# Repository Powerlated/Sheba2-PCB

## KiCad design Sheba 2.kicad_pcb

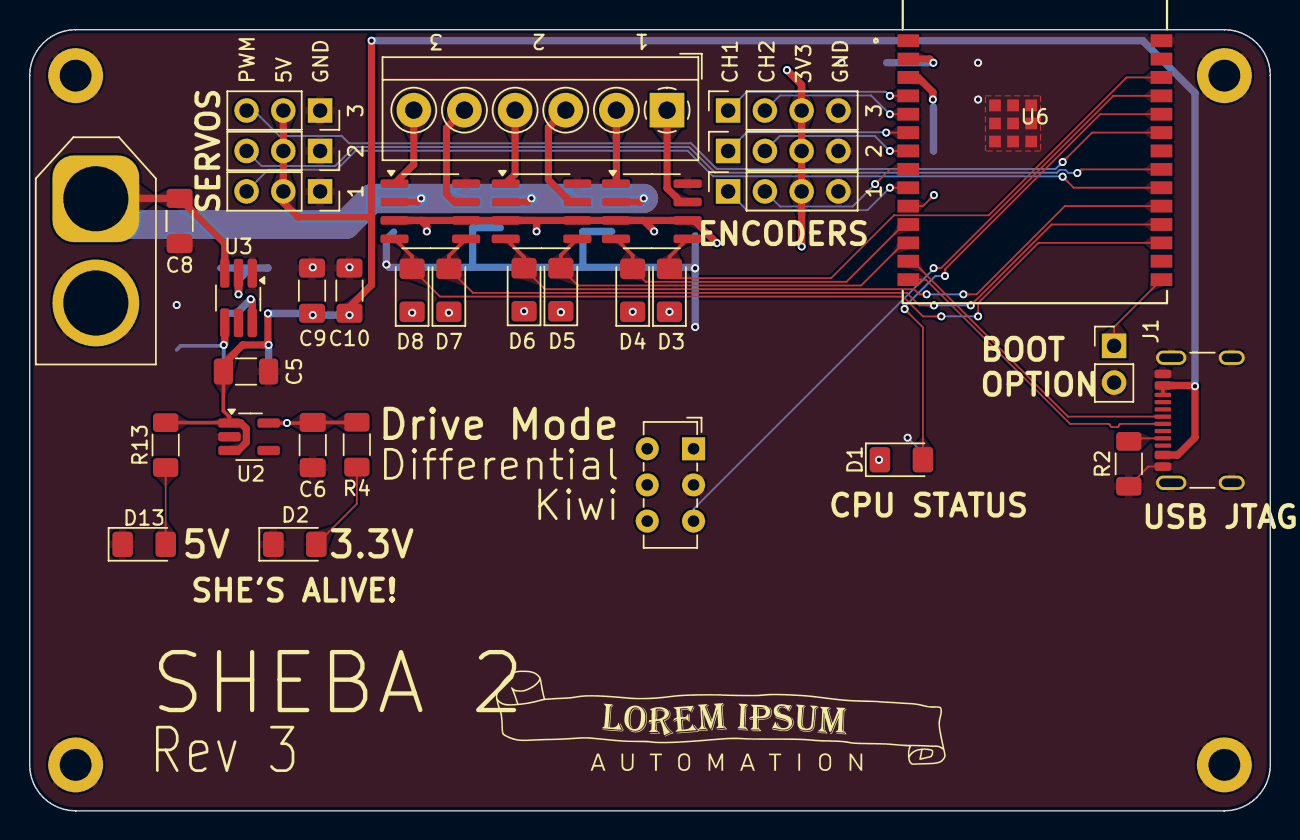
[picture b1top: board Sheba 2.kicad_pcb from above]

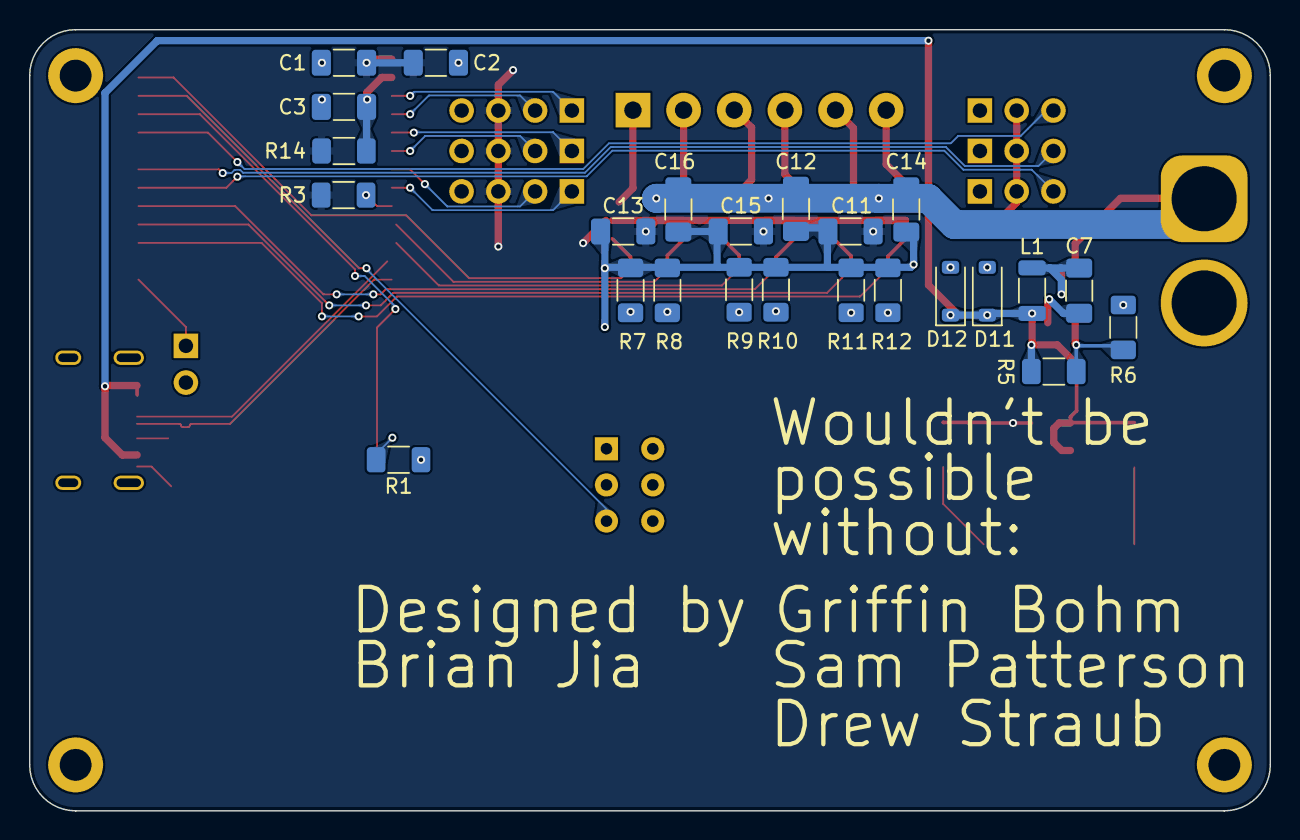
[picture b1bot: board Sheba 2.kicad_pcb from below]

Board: 2 copper layers, 85.7 x 54.0 mm, 62 parts (24 on the bottom side), 45 nets.

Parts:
Battery1: XT-60; AMASS_XT60-F_1x02_P7.20mm_Vertical
C1, C8, C9, C10: C22uF; C_1206_3216Metric_Pad1.33x1.80mm_HandSolder
C2, C3, C5, C6, C7, C11, C12, C13, C14, C15, C16: C1uF; C_1206_3216Metric_Pad1.33x1.80mm_HandSolder
D1, D2, D3, D5, D7, D13: LED Green; LED_1206_3216Metric_Pad1.42x1.75mm_HandSolder
D4, D6, D8: LED Red; LED_1206_3216Metric_Pad1.42x1.75mm_HandSolder
D11, D12: D_Zener5V; D_SOD-123
EP1, EP2, EP3: Conn_01x04_Socket; PinSocket_1x04_P2.54mm_Vertical
H1, H2, H3, H4: MountingHole_Pad; MountingHole_2.2mm_M2_DIN965_Pad
J1: Conn_01x02_Pin; PinHeader_1x02_P2.54mm_Vertical
J4, J5, J6: Conn_01x03_Pin; PinSocket_1x03_P2.54mm_Vertical
L1: L3.3uH; L_1206_3216Metric
MD1, MD2, MD3: ZXBM5210-S; SOIC-8_3.9x4.9mm_P1.27mm
Motor Terminal1: 6x Motor Port; TerminalBlock_4Ucon_1x06_P3.50mm_Horizontal
P1: USB 2.0 Type-C Port; USB_C_Receptacle_GCT_USB4105-xx-A_16P_TopMnt_Horizontal
R1, R4, R7, R8, R9, R10, R11, R12, R13: R220; R_1206_3216Metric_Pad1.30x1.75mm_HandSolder
R2: R5.11K; R_1206_3216Metric_Pad1.30x1.75mm_HandSolder
R3, R6, R14: R10k; R_1206_3216Metric_Pad1.30x1.75mm_HandSolder
R5: R56.2k; R_1206_3216Metric_Pad1.30x1.75mm_HandSolder
SW1: SPDT Switch; SW_E-Switch_EG1271_SPDT
U2: MIC5504-3.3YM5; SOT-23-5_HandSoldering
U3: AP62300TWU; TSOT-23-6_HandSoldering
U6: ESP32-C6-WROOM-1-N4; MOD28_ESP32-C6-WROOM-1_EXP

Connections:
+3V3: C1.2, C2.2, C6.1, C11.1, C13.1, C15.1, EP1.3, EP2.3, EP3.3, MD1.3 (VDD), MD1.6 (VREF), MD2.3 (VDD), MD2.6 (VREF), MD3.3 (VDD), MD3.6 (VREF), R3.1, R4.1, R14.1, U2.5 (VOUT), U6.2 (3V3)
+5V: C5.1, C9.1, C10.1, D11.1 (K), D12.1 (K), J4.2, J5.2, J6.2, L1.2, P1.A4 (VBUS), P1.A9 (VBUS), P1.B4 (VBUS), P1.B5 (VCONN), P1.B9 (VBUS), R5.1, R13.1, U2.1 (VIN), U2.3 (EN)
+BATT: Battery1.1 (+), C8.1, C12.1, C14.1, C16.1, MD1.2 (VM), MD2.2 (VM), MD3.2 (VM), U3.3 (IN)
/Power & Motors/M1_OUT1: MD3.7 (OUT2), Motor Terminal1.1
/Power & Motors/M1_OUT2: MD3.1 (OUT1), Motor Terminal1.2
/Power & Motors/M2_OUT1: MD2.7 (OUT2), Motor Terminal1.3
/Power & Motors/M2_OUT2: MD2.1 (OUT1), Motor Terminal1.4
/Power & Motors/M3_OUT1: MD1.7 (OUT2), Motor Terminal1.5
/Power & Motors/M3_OUT2: MD1.1 (OUT1), Motor Terminal1.6
BLINKY: D1.2 (A), U6.24 (RXD0)
BOOT_OPTION: J1.1, U6.15 (IO9)
EN: C3.2, R14.2, U6.3 (EN)
ENC1_1: EP1.1, U6.9 (IO1)
ENC1_2: EP1.2, U6.8 (IO0)
ENC2_1: EP2.1, U6.6 (IO6)
ENC2_2: EP2.2, U6.7 (IO7)
ENC3_1: EP3.1, U6.4 (IO4)
ENC3_2: EP3.2, U6.5 (IO5)
GND: Battery1.2 (-), C1.1, C2.1, C3.1, C5.2, C6.2, C8.2, C9.2, C10.2, C11.2, C12.2, C13.2, C14.2, C15.2, C16.2, D2.1 (K), D11.2 (A), D12.2 (A), D13.1 (K), EP1.4, EP2.4, EP3.4, H1.1, H2.1, H3.1, H4.1, J1.2, J4.1, J5.1, J6.1, MD1.8 (GND), MD2.8 (GND), MD3.8 (GND), P1.A1 (GND), P1.A12 (GND), P1.B1 (GND), P1.B12 (GND), P1.S1 (SHIELD), R1.2, R2.1, R6.2, R7.2, R8.2, R9.2, R10.2, R11.2, R12.2, SW1.2 (B), U2.2 (GND), U3.1 (GND), U6.1 (GND), U6.28 (GND), U6.29 (GND), U6.30 (GND), U6.31 (GND), U6.32 (GND), U6.33 (GND), U6.34 (GND), U6.35 (GND), U6.36 (GND), U6.37 (GND)
KIWI_DRIVE: SW1.3 (C), U6.25 (TXD0)
M1_FWD: D3.2 (A), MD3.5 (REV), U6.26 (IO3)
M1_REV: D4.2 (A), MD3.4 (FWD), U6.11 (IO10)
M2_FWD: D5.2 (A), MD2.5 (REV), U6.12 (IO11)
M2_REV: D6.2 (A), MD2.4 (FWD), U6.19 (IO21)
M3_FWD: D7.2 (A), MD1.5 (REV), U6.18 (IO20)
M3_REV: D8.2 (A), MD1.4 (FWD), U6.17 (IO19)
unnamed: D1.1 (K), R1.1
unnamed: D2.2 (A), R4.2
unnamed: D3.1 (K), R7.1
unnamed: D4.1 (K), R8.1
unnamed: D5.1 (K), R9.1
unnamed: D6.1 (K), R10.1
unnamed: D7.1 (K), R11.1
unnamed: D8.1 (K), R12.1
unnamed: D13.2 (A), R13.2
unnamed: P1.A5 (CC), R2.2
unnamed: C7.2, U3.6 (BST)
unnamed: R5.2, R6.1, U3.4 (FB)
unnamed: C7.1, L1.1, U3.2 (SW)
unnamed: R3.2, U6.10 (IO8)
SERVO1: J6.3, U6.23 (IO15)
SERVO2: J4.3, U6.21 (IO23)
SERVO3: J5.3, U6.20 (IO22)
USB_D+: P1.A6 (D+), U6.14 (IO13)
USB_D-: P1.A7 (D-), U6.13 (IO12)

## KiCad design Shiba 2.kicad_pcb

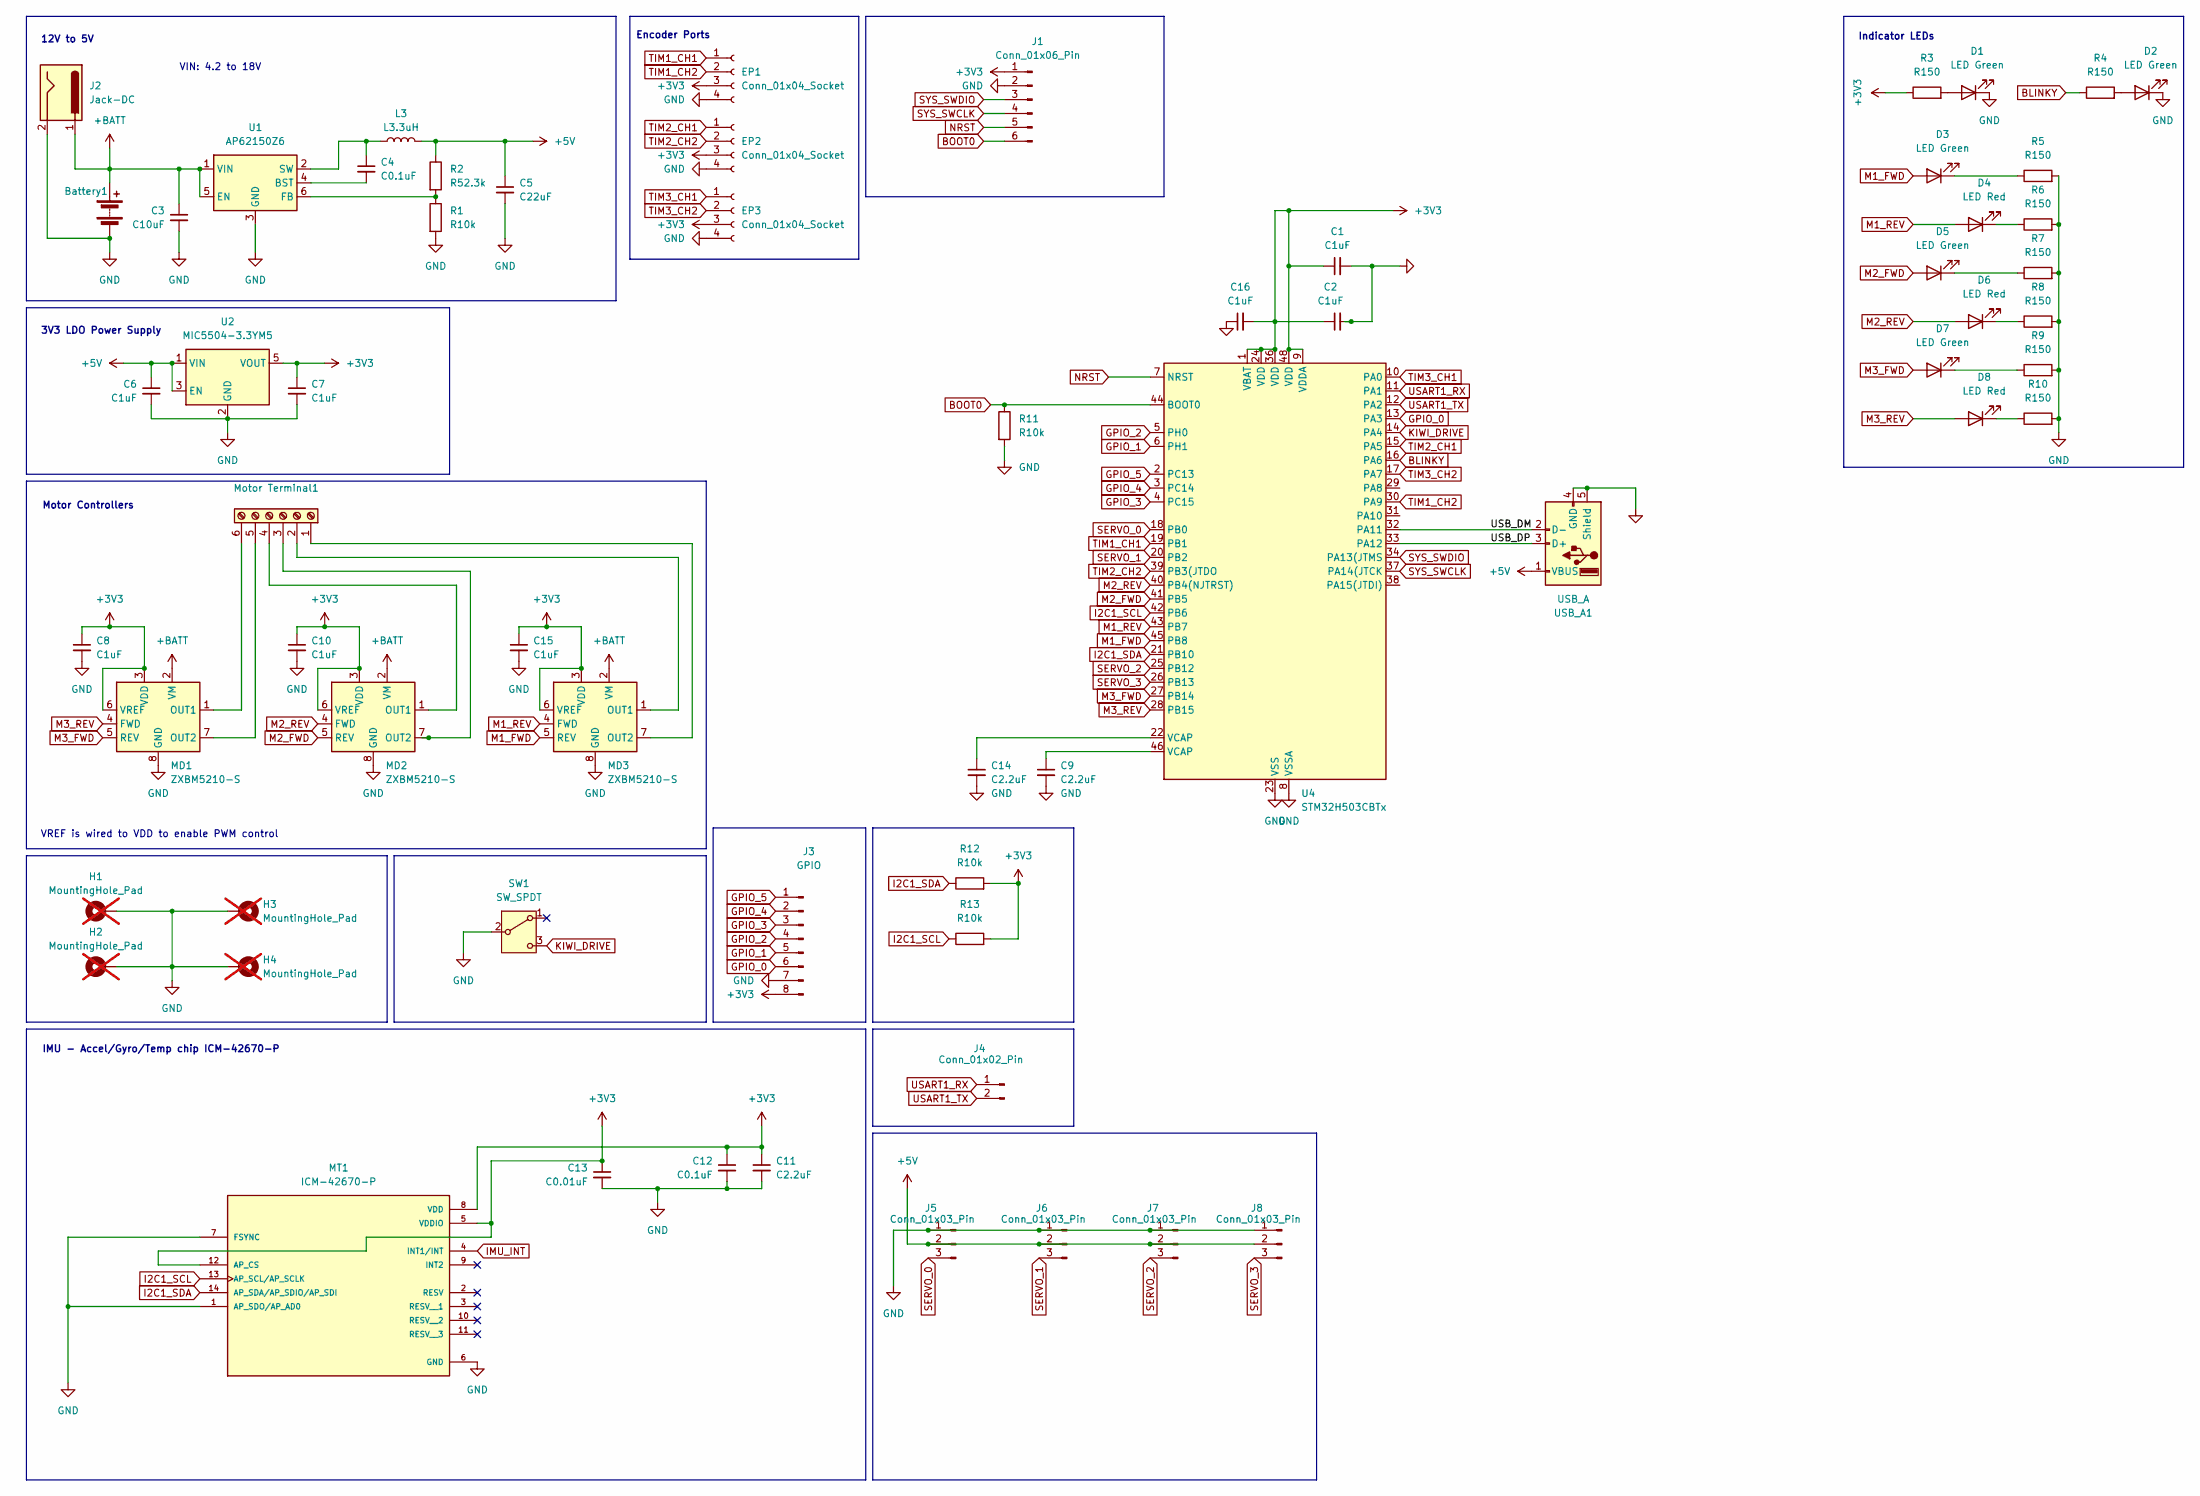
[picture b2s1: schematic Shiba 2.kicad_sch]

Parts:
Battery1: AMASS_XT60-F_1x02_P7.20mm_Vertical; DigiKey PRT-10474
C1, C2, C6, C7, C8, C10, C15, C16: C1uF; C_1206_3216Metric_Pad1.33x1.80mm_HandSolder; DigiKey CL31B105KBHNNNE
C3: C10uF; C_1206_3216Metric_Pad1.33x1.80mm_HandSolder; DigiKey CL31B106KOHNNWE
C4, C12: C0.1uF; C_1206_3216Metric_Pad1.33x1.80mm_HandSolder; DigiKey C1206C104K5RAC7800
C5: C22uF; C_1206_3216Metric_Pad1.33x1.80mm_HandSolder; DigiKey CL31A226MOCLNNC
C9, C14: C2.2uF; C_1206_3216Metric_Pad1.33x1.80mm_HandSolder; DigiKey CL31B105KBHNNNE
C11: C2.2uF; C_1206_3216Metric_Pad1.33x1.80mm_HandSolder; DigiKey CL31B225KBHNFNE
C13: C0.01uF; C_1206_3216Metric_Pad1.33x1.80mm_HandSolder; DigiKey C1206C103K5RAC7025
D1, D2, D3, D5, D7: LED Green; LED_1206_3216Metric_Pad1.42x1.75mm_HandSolder; DigiKey 150120VS75000
D4, D6, D8: LED Red; LED_1206_3216Metric_Pad1.42x1.75mm_HandSolder; DigiKey 150120RS75000
EP1, EP2, EP3: Conn_01x04_Socket; PinSocket_1x04_P2.54mm_Vertical; DigiKey 2.54mm Pin Socket
H1, H2, H3, H4: MountingHole_Pad; MountingHole_2.2mm_M2_DIN965_Pad; not fitted
J1: Conn_01x06_Pin; PinHeader_1x06_P2.54mm_Vertical; DigiKey 2.54mm Pin Header
J2: Jack-DC; BarrelJack_CUI_PJ-063AH_Horizontal; DigiKey PJ-037A
J3: GPIO; PinSocket_1x08_P2.54mm_Vertical; DigiKey 2.54mm Pin Socket
J4: Conn_01x02_Pin; PinHeader_1x02_P2.54mm_Vertical; DigiKey 2.54mm Pin Socket
J5, J6, J7, J8: Conn_01x03_Pin; PinSocket_1x03_P2.54mm_Vertical; DigiKey 2.54mm Pin Socket
L3: L3.3uH; L_1206_3216Metric; DigiKey LQM31PN3R3M00L
MD1, MD2, MD3: ZXBM5210-S; SOIC-8_3.9x4.9mm_P1.27mm; DigiKey ZXBM5210-S-1
MT1: ICM-42670-P; XDCR_ICM-42670-P; PARTREV 1.1; DigiKey ICM-42670-P
Motor Terminal1: TerminalBlock_4Ucon_1x06_P3.50mm_Horizontal; DigiKey OQ0612510000G
R1, R11, R12, R13: R10k; R_1206_3216Metric_Pad1.30x1.75mm_HandSolder; DigiKey RC1206FR-0710KL
R2: R52.3k; R_1206_3216Metric_Pad1.30x1.75mm_HandSolder; DigiKey CRCW120652K3FKEA
R3, R4, R5, R6, R7, R8, R9, R10: R150; R_1206_3216Metric_Pad1.30x1.75mm_HandSolder; DigiKey P150BCCT-ND
SW1: SW_SPDT; SW_E-Switch_EG1271_SPDT; DigiKey EG1271A
U1: AP62150Z6; SOT-563; DigiKey AP62150Z6-7
U2: MIC5504-3.3YM5; SOT-23-5; DigiKey MIC5504-3.3YM5
U4: STM32H503CBTx; LQFP-48_7x7mm_P0.5mm
USB_A1: USB_A; USB_A_Receptacle_GCT_USB1046; DigiKey USB-A1HSB6

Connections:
+3V3: C1.1, C2.1, C7.1, C8.1, C10.1, C11.1, C12.1, C13.1, C15.1, C16.2, EP1.3, EP2.3, EP3.3, J1.1, J3.8, MD1.3 (VDD), MD1.6 (VREF), MD2.3 (VDD), MD2.6 (VREF), MD3.3 (VDD), MD3.6 (VREF), MT1.5 (VDDIO), MT1.8 (VDD), MT1.12 (AP_CS), R3.1, R12.2, R13.2, U2.5 (VOUT), U4.1 (VBAT), U4.9 (VDDA), U4.24 (VDD), U4.36 (VDD), U4.48 (VDD)
+5V: C5.1, C6.1, J5.2, J6.2, J7.2, J8.2, L3.2, R2.1, U2.1 (VIN), U2.3 (EN), USB_A1.1 (VBUS)
+BATT: Battery1.1 (+), C3.1, J2.1, MD1.2 (VM), MD2.2 (VM), MD3.2 (VM), U1.1 (VIN), U1.5 (EN)
/USB_DM: U4.32 (PA11), USB_A1.2 (D-)
/USB_DP: U4.33 (PA12), USB_A1.3 (D+)
BLINKY: R4.1, U4.16 (PA6)
BOOT0: J1.6, R11.1, U4.44 (BOOT0)
GND: Battery1.2 (-), C1.2, C2.2, C3.2, C5.2, C6.2, C7.2, C8.2, C9.2, C10.2, C11.2, C12.2, C13.2, C14.2, C15.2, C16.1, D1.1 (K), D2.1 (K), EP1.4, EP2.4, EP3.4, H1.1, H2.1, H3.1, H4.1, J1.2, J2.2, J3.7, J5.1, J6.1, J7.1, J8.1, MD1.8 (GND), MD2.8 (GND), MD3.8 (GND), MT1.1 (AP_SDO/AP_AD0), MT1.6 (GND), MT1.7 (FSYNC), R1.2, R5.2, R6.2, R7.2, R8.2, R9.2, R10.2, R11.2, SW1.2 (B), U1.3 (GND), U2.2 (GND), U4.8 (VSSA), U4.23 (VSS), U4.35 (VSS), U4.47 (VSS), USB_A1.4 (GND), USB_A1.5 (Shield)
GPIO_0: J3.6, U4.13 (PA3)
GPIO_1: J3.5, U4.6 (PH1)
GPIO_2: J3.4, U4.5 (PH0)
GPIO_3: J3.3, U4.4 (PC15)
GPIO_4: J3.2, U4.3 (PC14)
GPIO_5: J3.1, U4.2 (PC13)
I2C1_SCL: MT1.13 (AP_SCL/AP_SCLK), R13.1, U4.42 (PB6)
I2C1_SDA: MT1.14 (AP_SDA/AP_SDIO/AP_SDI), R12.1, U4.21 (PB10)
IMU_INT: MT1.4 (INT1/INT)
KIWI_DRIVE: SW1.3 (C), U4.14 (PA4)
M1_FWD: D3.2 (A), MD3.5 (REV), U4.45 (PB8)
M1_REV: D4.2 (A), MD3.4 (FWD), U4.43 (PB7)
M2_FWD: D5.2 (A), MD2.5 (REV), U4.41 (PB5)
M2_REV: D6.2 (A), MD2.4 (FWD), U4.40 (PB4(NJTRST))
M3_FWD: D7.2 (A), MD1.5 (REV), U4.27 (PB14)
M3_REV: D8.2 (A), MD1.4 (FWD), U4.28 (PB15)
NRST: J1.5, U4.7 (NRST)
unnamed: C9.1, U4.46 (VCAP)
unnamed: C14.1, U4.22 (VCAP)
unnamed: D1.2 (A), R3.2
unnamed: D2.2 (A), R4.2
unnamed: D3.1 (K), R5.1
unnamed: D4.1 (K), R6.1
unnamed: D5.1 (K), R7.1
unnamed: D6.1 (K), R8.1
unnamed: D7.1 (K), R9.1
unnamed: D8.1 (K), R10.1
unnamed: MD1.1 (OUT1), Motor Terminal1.6
unnamed: MD1.7 (OUT2), Motor Terminal1.5
unnamed: MD2.1 (OUT1), Motor Terminal1.4
unnamed: MD2.7 (OUT2), Motor Terminal1.3
unnamed: MD3.1 (OUT1), Motor Terminal1.2
unnamed: MD3.7 (OUT2), Motor Terminal1.1
unnamed: C4.2, U1.4 (BST)
unnamed: R1.1, R2.2, U1.6 (FB)
unnamed: C4.1, L3.1, U1.2 (SW)
SERVO_0: J5.3, U4.18 (PB0)
SERVO_1: J6.3, U4.20 (PB2)
SERVO_2: J7.3, U4.25 (PB12)
SERVO_3: J8.3, U4.26 (PB13)
SYS_SWCLK: J1.4, U4.37 (PA14(JTCK)
SYS_SWDIO: J1.3, U4.34 (PA13(JTMS)
TIM1_CH1: EP1.1, U4.19 (PB1)
TIM1_CH2: EP1.2, U4.30 (PA9)
TIM2_CH1: EP2.1, U4.15 (PA5)
TIM2_CH2: EP2.2, U4.39 (PB3(JTDO)
TIM3_CH1: EP3.1, U4.10 (PA0)
TIM3_CH2: EP3.2, U4.17 (PA7)
USART1_RX: J4.1, U4.11 (PA1)
USART1_TX: J4.2, U4.12 (PA2)

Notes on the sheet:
IMU - Accel/Gyro/Temp chip ICM-42670-P
Indicator LEDs
12V to 5V
Encoder Ports
VIN: 4.2 to 18V
VREF is wired to VDD to enable PWM control
Motor Controllers
3V3 LDO Power Supply

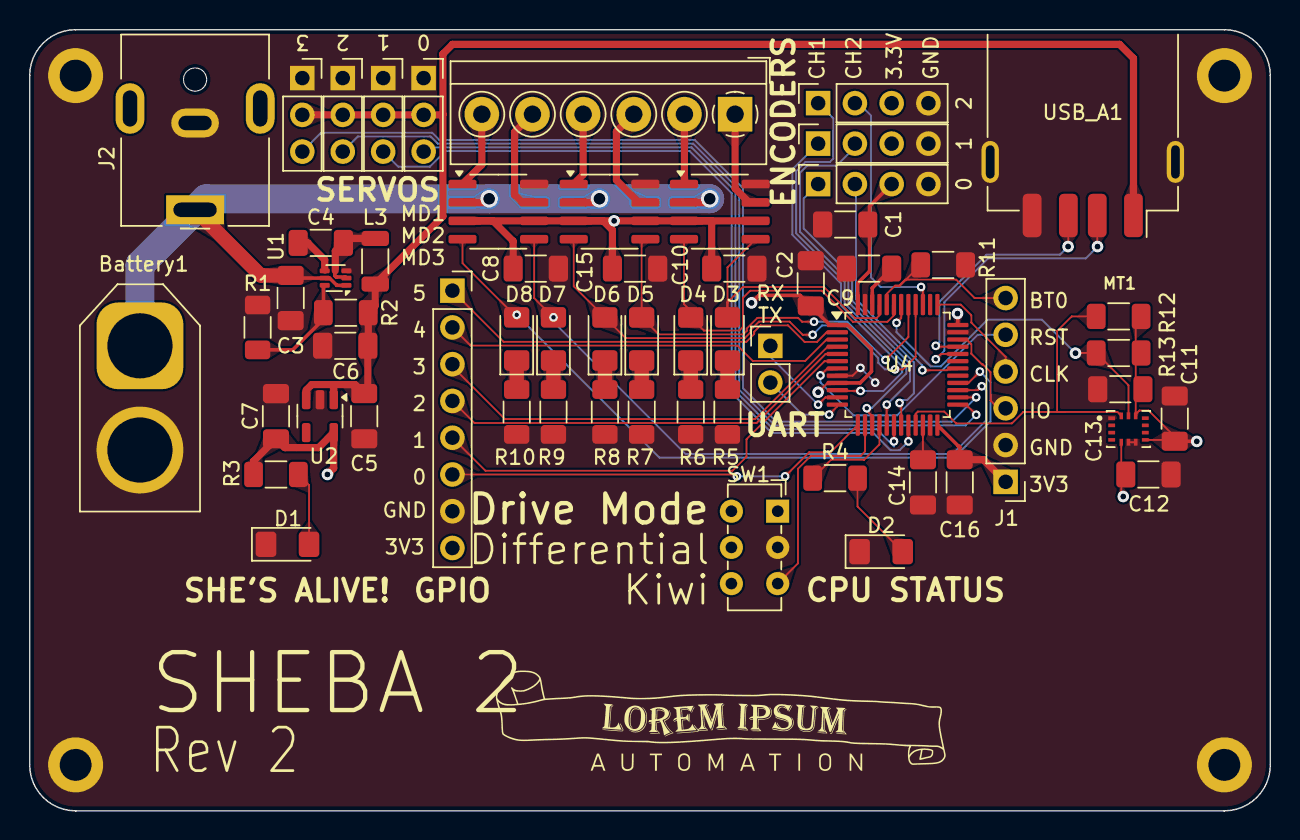
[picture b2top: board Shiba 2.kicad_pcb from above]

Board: 2 copper layers, 85.7 x 54.0 mm, 64 parts (0 on the bottom side), 57 nets.

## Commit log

2024-04-21 Working on it!
2024-04-21 add schematic files back (oops)
2024-04-22 About ready to order but I realized I used underpowered motor drivers
2024-04-22 REV 1 ORDERED WOOOOO
2024-04-22 Add .gitignore
2024-04-22 Remove gitignored files
2024-04-22 going to prepare BOM for Rev 1 order
2024-04-22 Rev 1 BOM ordered let's goooooo!
2024-04-22 Rev 1 BOM order save
2024-04-23 Rev 2 maybe?
2024-04-23 more rev2 revisions
2024-04-23 Rename Shiba to Sheba
2024-04-24 Preparing to remove USB port and switch to STM32F072CBTx
2024-04-24 Rev 2 ordered!
2024-04-27 Post-rev 2 changes
2024-04-27 Getting ready to add overvoltage/ESD protection
2024-04-27 Actually get ready to add protections
2024-04-27 Ready to finalize Rev3
2024-04-27 Rev3 ready to order
2024-04-29 Rewire the entire thing to use hardware PWM and software quadrature decoding
2024-05-01 ig we switching to esp32 now
2024-05-03 change to ESP32-C6-WROOM
2024-05-25 i forgor
